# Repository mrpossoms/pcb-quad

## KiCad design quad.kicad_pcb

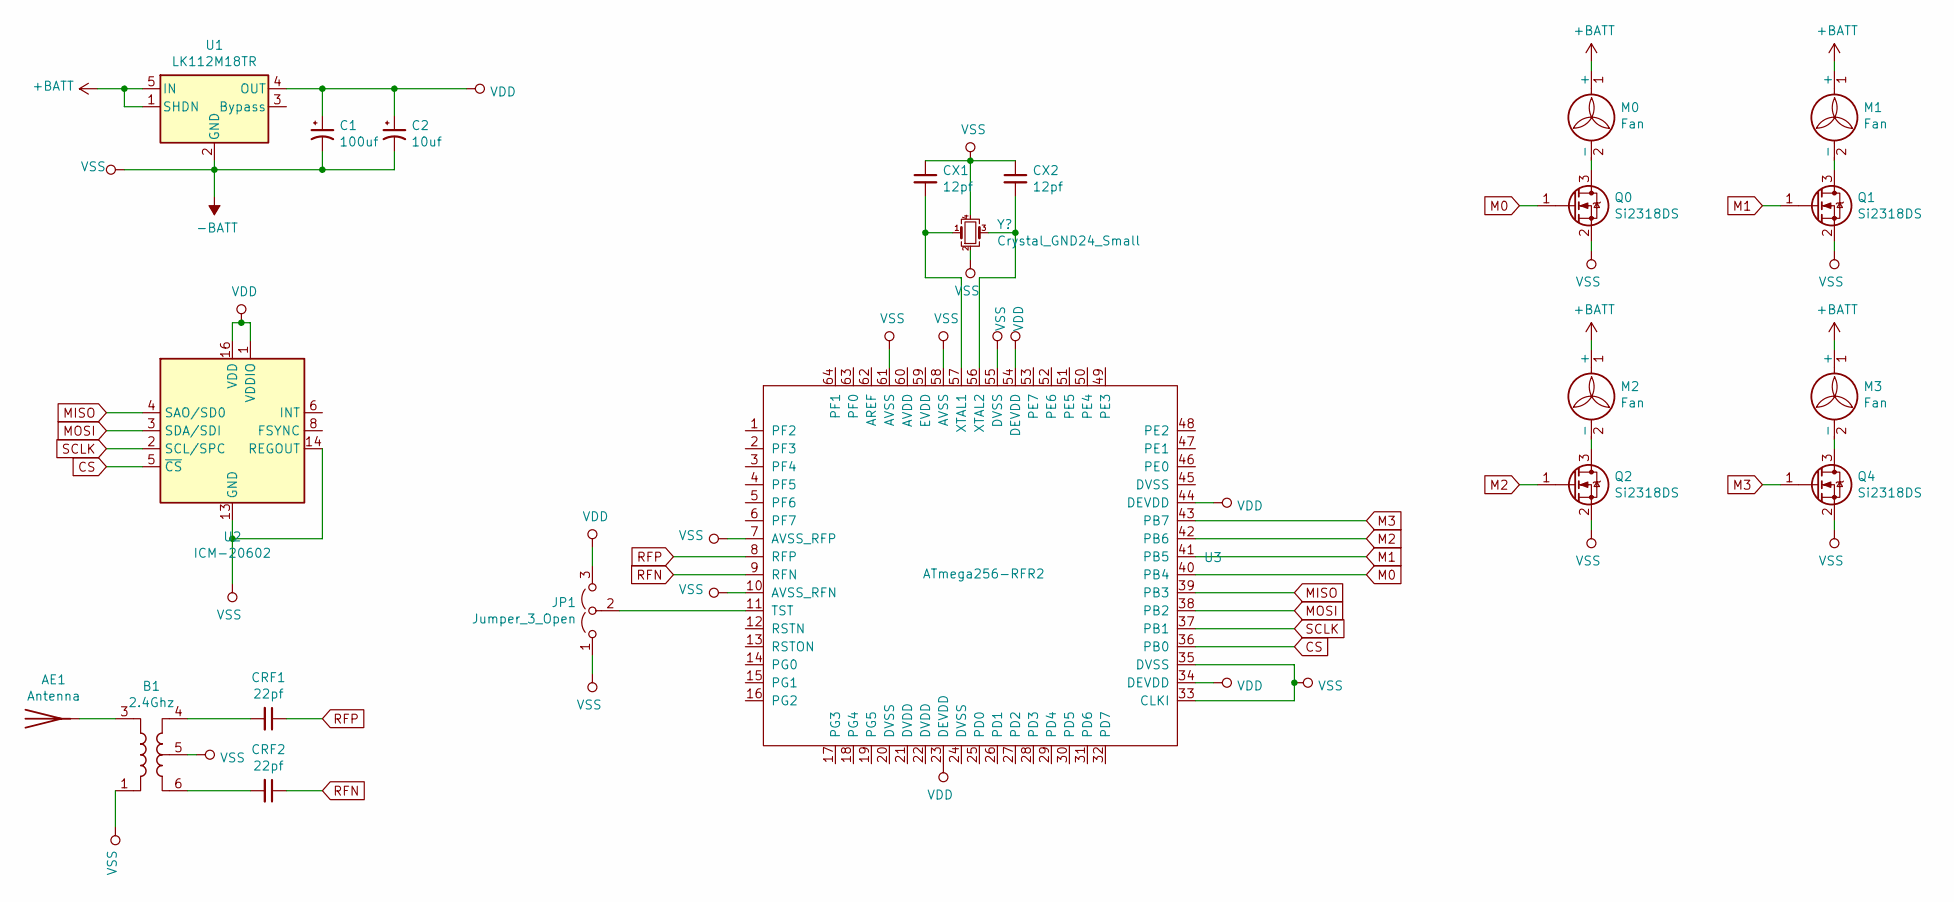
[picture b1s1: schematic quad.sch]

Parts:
AE1: Antenna; PinHeader_1x01_P1.00mm_Vertical
B1: 2.4Ghz; Mini-Circuits_CD541_H2.08mm
C1: 100uf; CP_EIA-7343-30_AVX-N
C2: 10uf; CP_EIA-2012-15_AVX-P
CRF1, CRF2: 22pf; C_0603_1608Metric
CX1, CX2: 12pf; C_0805_2012Metric
JP1: Jumper_3_Open; SolderJumper-3_P1.3mm_Open_Pad1.0x1.5mm
M0, M1, M2, M3: Fan; PinSocket_1x02_P2.00mm_Vertical
Q0, Q1, Q2, Q4: Si2318DS; SOT-23
U1: LK112M18TR; SOT-23-5
U2: ICM-20602; LGA-16_3x3mm_P0.5mm_LayoutBorder3x5y
U3: ATmega256-RFR2; QFN-64-1EP_9x9mm_P0.5mm_EP4.7x4.7mm

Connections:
+BATT: M0.1 (+), M1.1 (+), M2.1 (+), M3.1 (+), U1.1 (SHDN), U1.5 (IN)
-BATT: B1.1, B1.5, C1.2, C2.2, CX1.1, CX2.1, JP1.1 (A), Q0.2 (S), Q1.2 (S), Q2.2 (S), Q4.2 (S), U1.2 (GND), U2.9 (GND), U2.10 (GND), U2.11 (GND), U2.12 (GND), U2.13 (GND), U2.14 (REGOUT), U2.15 (GND), U3.7 (AVSS_RFP), U3.10 (AVSS_RFN), U3.33 (CLKI), U3.35 (DVSS), U3.55 (DVSS), U3.58 (AVSS), U3.61 (AVSS); also elsewhere on the board
CS: U2.5 (~CS), U3.36 (PB0)
M0: Q0.1 (G), U3.40 (PB4)
M1: Q1.1 (G), U3.41 (PB5)
M2: Q2.1 (G), U3.42 (PB6)
M3: Q4.1 (G), U3.43 (PB7)
MISO: U2.4 (SAO/SD0), U3.39 (PB3)
MOSI: U2.3 (SDA/SDI), U3.38 (PB2)
unnamed: AE1.1, B1.3
unnamed: B1.4, CRF1.2
unnamed: B1.6, CRF2.2
unnamed 12: CX1.2, U3.57 (XTAL1); also elsewhere on the board
unnamed 13: CX2.2, U3.56 (XTAL2); also elsewhere on the board
unnamed: JP1.2 (C), U3.11 (TST)
unnamed: M0.2 (-), Q0.3 (D)
unnamed: M1.2 (-), Q1.3 (D)
unnamed: M2.2 (-), Q2.3 (D)
unnamed: M3.2 (-), Q4.3 (D)
RFN: CRF2.1, U3.9 (RFN)
RFP: CRF1.1, U3.8 (RFP)
SCLK: U2.2 (SCL/SPC), U3.37 (PB1)
VDD: C1.1, C2.1, JP1.3 (B), U1.4 (OUT), U2.1 (VDDIO), U2.16 (VDD), U3.23 (DEVDD), U3.34 (DEVDD), U3.44 (DEVDD), U3.54 (DEVDD)

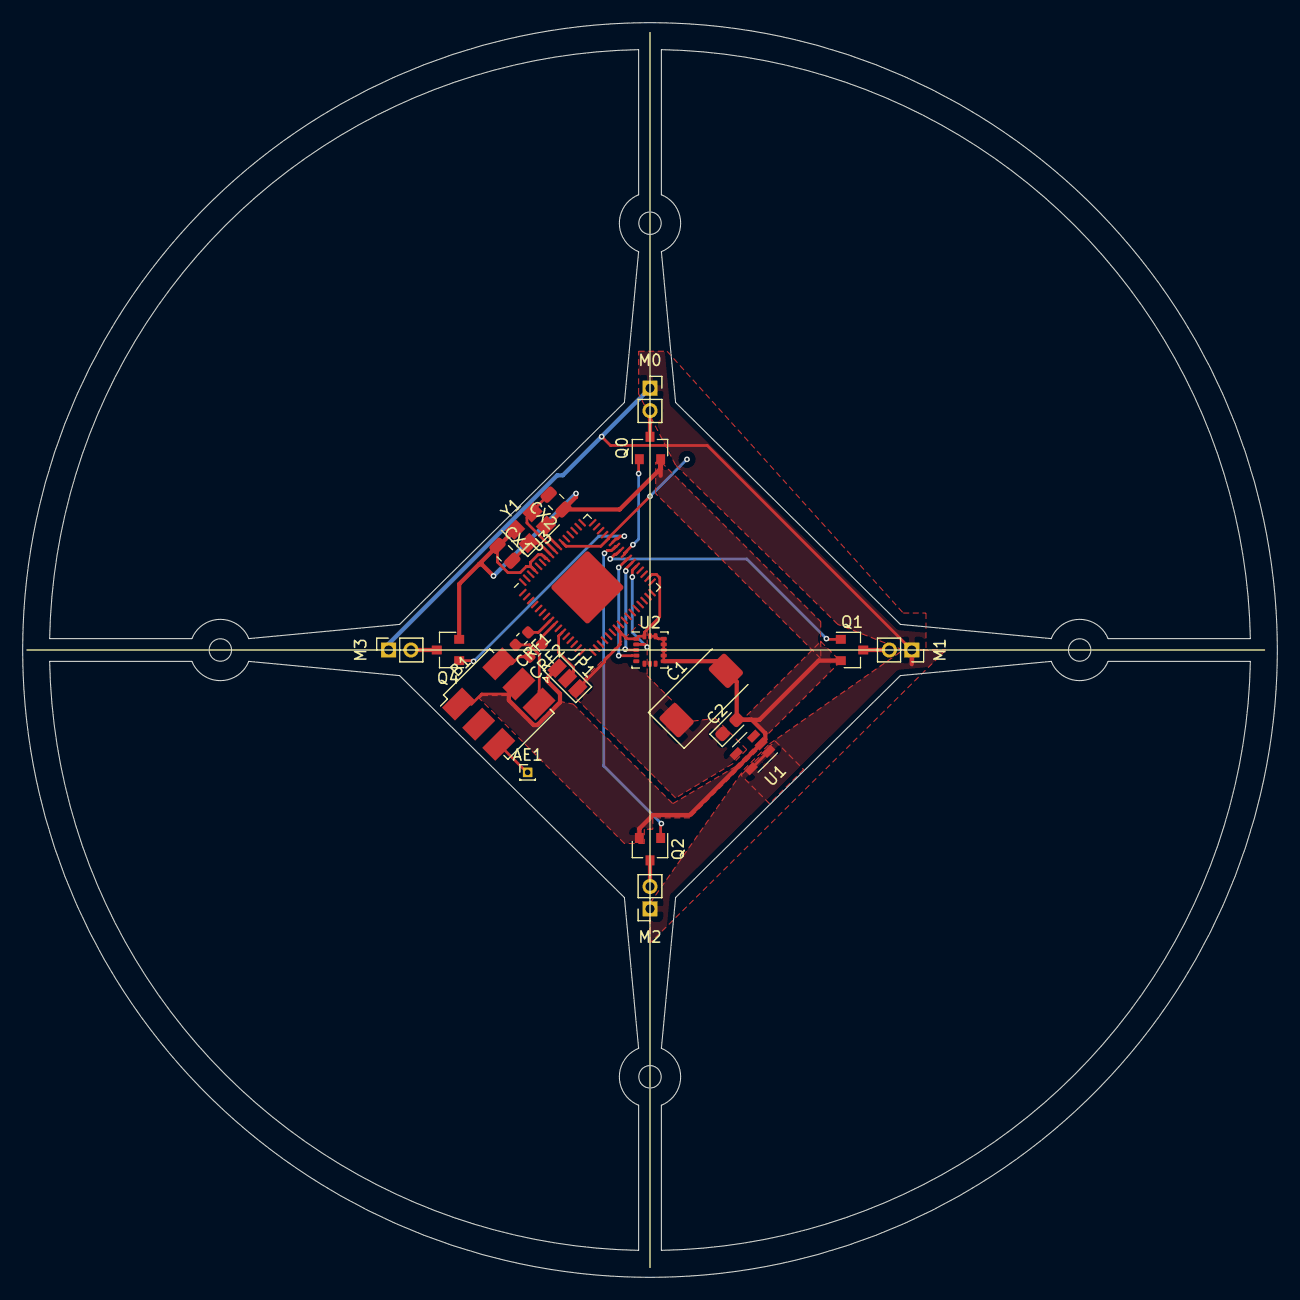
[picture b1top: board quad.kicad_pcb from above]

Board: 2 copper layers, 112.0 x 112.0 mm, 21 parts (0 on the bottom side), 23 nets.

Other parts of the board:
Y1: Crystal_GND24_Small; Crystal_SMD_3225-4Pin_3.2x2.5mm

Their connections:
-BATT: Y1.2, Y1.4; also elsewhere on the board
unnamed 12: Y1.1; also elsewhere on the board
unnamed 13: Y1.3; also elsewhere on the board

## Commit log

2020-01-21 Starting board layout
2020-01-22 Good board outline
2020-01-23 More board layout
2020-01-28 PWM demo
